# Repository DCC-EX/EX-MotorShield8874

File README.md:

# EX-Motorshield8874

## Overview

The EX-Motorshield8874 is a pin compatible with the original [Arduino Motor Shield Rev3](https://store.arduino.cc/products/arduino-motor-shield-rev3) but provides significantly improved electrical performance for driving higher loads, with lower power dissipation, and improved usability.

The EX-Motorshield8874 is based on two DRV8874 H-bridge motor drivers with integrated current sensing from Texas Instruments (TI). It is used to drive inductive loads like relays, solenoids, DC and stepping motors.

Powering of Arduino motherboard is possible due to the onboard DC/DC buck converter, supporting a wide input supply range from 9 to 30V. The reverse polarity protection prevents damage to the circuit and its components in case the power supply is accidentally connected with reversed polarity.

This Shield features a green status LED which provides a visual indication of the power supply status.

### Compatibility with [Arduino Motor Shield Rev3](https://store.arduino.cc/products/arduino-motor-shield-rev3)

The EX-MotorShield8874 is pin compatible with the original Arduino Motor Shield but provides significantly improved electrical performance for driving higher loads. Input voltage range is 9-30VDC and the maximum peak output is 5A per channel, in contrast to 5-12VDC and 2A peak for the original Arduino Motor Shield.

There is also almost no voltage drop incurred from the input voltage due to the MOSFET based design, unlike the bipolar L298 used in the Arduino Motor Shield. For DCC and DC PWM model railway use, a range of 10-24VDC is recommended depending on scale.

### Motor Driver Configuration for DCC-EX EX-CommandStation

The EX-MotorShield8874 will work with the `STANDARD_MOTOR_SHIELD` definitions in `MotorDrivers.h`, but that is not ideal for several reasons. It will both unnecessarily limit current output, ignore the fault pin, and not read current correctly.

The following motor definitions are required, and appear in later versions of EX-CommandStation, with the tag `EX8874_SHIELD`, which will differ according to whether the Command Station is an UNO or Mega with 5V 10-bit ADC, or a 3.3V capable system with 12-bit ADC:

```c++
// EX 8874 based shield connected to a 5V system (like Arduino UNO/Mega) and 10bit (1024) ADC
#define EX8874_SHIELD F("EX8874"), \
 new MotorDriver( 3, 12, UNUSED_PIN, 9, A0, 5.08, 5000, A4), \
 new MotorDriver(11, 13, UNUSED_PIN, 8, A1, 5.08, 5000, A5)

// EX 8874 based shield connected to a 3V3 system with 12-bit (4096) ADC
#define EX8874_SHIELD F("EX8874"), \
 new MotorDriver( 3, 12, UNUSED_PIN, 9, A0, 1.27, 5000, A4), \
 new MotorDriver(11, 13, UNUSED_PIN, 8, A1, 1.27, 5000, A5)
```

## Control Pin Assignments

### Default Pin Assignment for DCC-EX/Arduino motor control

The EX-MotorShield8874 has the following default pin assignment for control pins on the Arduino header, and is used for full Arduino Motor Shield R3 compatibility when used for DCC-EX EX-CommandStation.

| Function | Channel A Pin | Channel B Pin |
|-----------|-------|-------|
| PWM       | D3  | D11 |
| Direction | D12 | D13 |
| Brake     | D9  | D8 |
| Current sensing | A0 | A1 |
| Fault_N   | A4  | A5 |

Default pin assignment is used for DCC-EX command stations, and has the DRV8874 mode select pin `PMODE` = high.

### Alternative Pin Assignment for DCC-EX/Arduino motor control 

All motor control signals can be connected to two different Adruino header pins. Selecting between the default pin out and the alternative pin out is done via solder jumpers on the PCB which must be first cut to disable the default position, then solder applied to select the alternate position.

| Function | Channel A Pin | Channel B Pin |
|-----------|-------|-------|
| PWM       | D2  | D5 |
| Direction | D10 | D4 |
| Brake     | D7  | D6 |
| Current sensing | A2 | A3 |
| Fault_N   | D0  | D1 |

NB: For DCC-EX control, these are not ideal pin assignments and are intended for future support of stacking of two shields. Further documentation updates will be available once testing of this mode is complete.

### Fault indicator

The H-Bridges are protected against supply undervoltage, charge pump undervoltage, output overcurrent and device overtemperature. Fault conditions are indicated on the pin `nFAULT` of the H-Bridge driver. The open drain output of the fault indicator is pulled low during a fault condition and pulled to high with the on board pull-up resistor. There is one fault indicator per channel.

**NOTE for UNO users:** the `nFAULT` pins are routed to the same pins used for I2C on the ATMEGA329P used on the Arduino UNO R3, namely A4 and A5. As such, if you are to use an EX-MotorShield8874 on an Arduino UNO, please cut the default track on the relevant jumpers to disable them. If you want to use the `nFault` pins you will need to manually jumper them to any available alternate digital input pins, then configure the Motor Driver entry in EX-CommandStation to suit the pins used.

### Alternative pin assignment for other motor control applications

The alternative pin assignment for motor control (PH/EN mode) allows to control the motor in a speed and direction type interface. This mode is selected via Jumper J101 (DRV8874 mode select pin `PMODE` = low) and is NOT required for use with DCC-EX. It is documented for completeness.

| Function | Channel A Pin | Channel B Pin |
|-----------|-------|-------|
| PH       | D3  | D11 |
| EN       | D12 | D13 |
| Brake     | D9  | D8 |
| Current sensing | A0 | A1 |
| Fault_N   | A4  | A5 |

## Electrical Parameters

The DCC-EX Motor Shield provides the following electrical parameters.

| Parameter | Value |
|-----------|-------|
| Operating voltage range | 9-30VDC, polarity protected|
| Maximum H-bridge current  | 5A peak per channel |
| Arduino supply voltage output (VIN) | 7.2V@2A max |
| IO voltage              | 3.3 and 5V, using IOREF by default |
| I2C connectivity        | Dupont, 2.54mm dual row pin, and STEMMA QT/Qwiic Headers |
| Current sensing         | Yes, adjusts range to IOREF voltage |
| Control modes possible | PWM, by default, PH/EN via jumper |

## Current Sensing

Current sensing is independently available for each channel. The Arduino IOREF supply voltage is sensed automatically, and adjusts the gain factor for the current sensing to take advantage of the full ADC input voltage range for 5V or 3.3V microcontrollers. The sense factors are calculated as follows for DCC-EX motor driver definitions:

| IOREF Voltage: | 5V | 3V3 |
|----------------|----|-----|
| 10-bit ADC, 1024 count | 5.08 | 4.94 |
| 12-bit ADC, 4096 count | 1.27 | 1.24 |

These values have been incorporated into EX-CommandStation Motor Driver definitions, so selecting `EX8874_SHIELD` as the `MOTOR_SHIELD_TYPE` in config.h will configure it correctly.

## Track LEDs

LEDs are provided for each channel, indicating the corresponding H-Bridge is supplying power to output connectors.

## Header Pin Assignments

The following pin assignments have been used for the various connectors.

### I2C Headers

Three I2C expansion headers (Dupont, dual-row 8-pin, and STEMMA QT/Qwiic) allow connecting either an OLED display or other additional I2C based devices.

#### Arduino Header

On the Arduino header, the default upper right I2C pins are used for I2C:

| Function | UNO R3 Pin | Mega Pin |
|-----------|-------|-------|
| SCL | D18/A5 | D21 |
| SDA | D19/A4 | D20 |

#### DIP Header

The dual-row 8-pin header has the following pin assignments:

| Function | Odd Pin | Even Pin |
|-----------|-------|-------|
| IOREF | 1 | 2 |
| SDA | 3 | 4 |
| GND | 5 | 6 |
| SCL | 7 | 8 |

#### OLED Header

The single-row 4-pin OLED header has the following pin assignments, which are standard for many I2C capable OLED displays:

| Function | Pin |
|-----------|-------|
| GND | 1 |
| IOREF | 2 |
| SCL | 3 |
| SDA | 4 |

#### STEMMA QT/Qwiic Connector

STEMMA QT/Qwiic connector pin assignments are per the standard, but included for completeness:

| Function | Pin | Colour Code |
|-----------|-------|-------|
| GND | 1 | Black |
| 3v3 | 2 | Red |
| SDA | 3 | Blue |
| SCL | 4 | Yellow |

**NOTE** STEMMA QT power is tied to 3v3 as that is required for the standard. When using the EX-MotorShield8874 with 5V motherboards such as UNO and Mega, any I2C peripherals connected to the STEMMA QT connector **must** be 5V-tolerant only!

Pull-up resistors for the I2C communication are not populated by default. If required, pull-up resistors (R101, R102) can be populated on the board, though this is typically not necessary.

## Reset button

A reset button is provided to reset the Arduino board.

## PCB Jumpers

Various PCB jumpers are provided to alter functionality of the board to suit user needs. These include jumpers to alter pin assignments for driving the motor shield, to disable the onboard 7.2V regulator or disconnect it from the VIN, and jumpers to override the IOREF pin for ADC range selection.

### Aternate Pin Assignment PCB Jumpers

There are 5 sets of PCB jumpers for each motor driver IC, some or all of which can be used to reassign Arduino pins to the various logic functions. The table below lists them in order as they appear on the PCB:

| Function | Driver A Default | Driver A Alternate| Driver B Default | Driver B Alternate |
|----------|---------|----------|---------|-----------|
| PWM       | D3  | D2 | D11 | D5 |
| Fault | A4  | D0 | A5 | D1 |
| Brake | D9  | D7 | D8 | D6 |
| Direction | D12 | D10 | D13 | D4 |
| Current sense | A0 | A2 | A1 | A3 |

### Power Configuration PCB Jumpers

There are 4 sets of PCB jumpers to change the way power is handled on the board. One on the top of the board, and 3 on the bottom, shown here:

| Jumper | Function |
|--------|----------|
| Regulator Disable (Regulator Enable on Rev A boards) | Defaults to *ENABLED*. Rev B boards, *solder* between pads to DISABLE onboard 7.2V regulator. Rev A boards *cut* between pads to DISABLE |
| IOREF Override | Defaults to IOREF used as power source, cut and then solder to either 5V or 3V3 to power logic and current sense |
| VM to Vin Enable (unlabelled on Rev A boards) | Defaults to NOT connected. CAUTION: soldering these pads CONNECTS motor power to VIN and should not be needed |
| VIN | Defaults to ON, cut to stop providing regulated 7.2V power to VIN to power the Arduino |

## Manufacturing Notes

### Bill of Materials (BOM)

The bill of materials spreadsheet above is optimised for manufacture at JLCPCB (https://jlcpcb.com/) at present, and will allow assembly of all components except the DC barrel jack, motor output connectors and Arduino shield stackable headers.

### PCB Material Specifications

For best performance, 1oz copper for both outer and inner layers of this 4-layer PCB are safest. Of course 2oz copper can be specified, but this is not deemed necessary from testing so far and cost may be prohibitive. Also, using FR-4 TG155 will give additional safety margin. The design can be made lead-free, provided all components are also lead-free types. JLCPCB currently does not have lead-free connectors for DCC track or DC input power, so those components are not in the default Bill of Materials (BOM).

## Stacking Multiple Shields

It is possibile to stack two EX-MotorShield8874s, and even stack an EX-MotorShield and a Arduino Motor Shield.

There are two different proposed operating modes possible:

1. **Independent district mode:** The DCC-EX Motor Shields are controlled independently using different control signals. This allows a total 4 independent H-Bridges to be driven completely independently for separate DCC or DC PWM districts.
2. **Parallel booster mode:** Both EX-MotorShield8874s are controlled with the same control signals so both pairs of H-bridges are running in parallel. This mode is used to increase the current capabilities of the 2 DCC or DC PWM districts.

***CAUTIONARY NOTE:*** Only one EX-MotorShield8874 should provide power to the underlying motherboard from the DCC power feed! The jumper connecting the top VIN feed pin from the onboard 7.2V regulator to the Arduino sheild connectors must be cut on one of the stacked shields. It is also advisable to cut the ENABLE pin for the onboard regulator as that will turn it off completely as well. (See documentation of Power Configuration PCB Jumpers, above!)

This information is provided for reference. For full documentation, please visit this section on our website; [Stacking EX-MotorShields](https://dcc-ex.com/reference/hardware/motorboards/ex-motor-shield-8874.html#stacking-ex-motorshield8874s)

## Version History

**Rev B2**
* Changed the AOD4185 reverse voltage protection mosfet (Q201) in a TO-252-2 package to an AO4407C in an SOIC-8 package to save board space.

**Rev B**
* Changed 7.2V Regulator from MP9942GJ-Z to TPS54302 due to availability issues. NOTICE: This forced the Regulator Enable/Disable to be reversed from the Rev A board. The Rev A board jumper pad must be *cut* to disable the regulator and is named "Regulator Enable". On the Rev B board, the jumper must be *solder bridged* to to disable the regulator and is labelled "7V Regulator Disable".
* The regulator change necessitated changing Inductor L201 from 56uH to 15uH.

**Rev A2**
* Added 47k pulldown resistors (R103 and R104) to the enable pins to prevent possible DCC or DC voltage pulses to the outputs until the command station is able to set the GPIO pins to a stable state during boot up.
* Added more descriptive silkscreen labelling.
* Removed solder mask from jumper pads to make it easier to see which are bridged and which are open.

**Rev A**
* First version of the EX-MotorShield8874. NOTICE: It may be necessary to add 47k pulldown resistors between pwm_a and pwm_b and GND. These are the "enable" pins that turn power on to the track outputs. With the pins floating, it is possible that brief DC power can be applied to the track until the command station fully boots. If configured for the STANDARD_MOTOR_SHIELD, this is as simple as inserting one end of a resistor into pin 3 of the header and the other end to a GND header pin, and the other resister between pin 11 and GND. If using a different motor driver definition, use the enable pins for that definition.

## Reference

- [Schematic](./static_images/EX-MotorShield8874Schematic_RevB2.pdf)
- [DRV8874 Datasheet](https://www.ti.com/product/DRV8874?keyMatch=DRV8874&tisearch=search-everything&usecase=GPN)

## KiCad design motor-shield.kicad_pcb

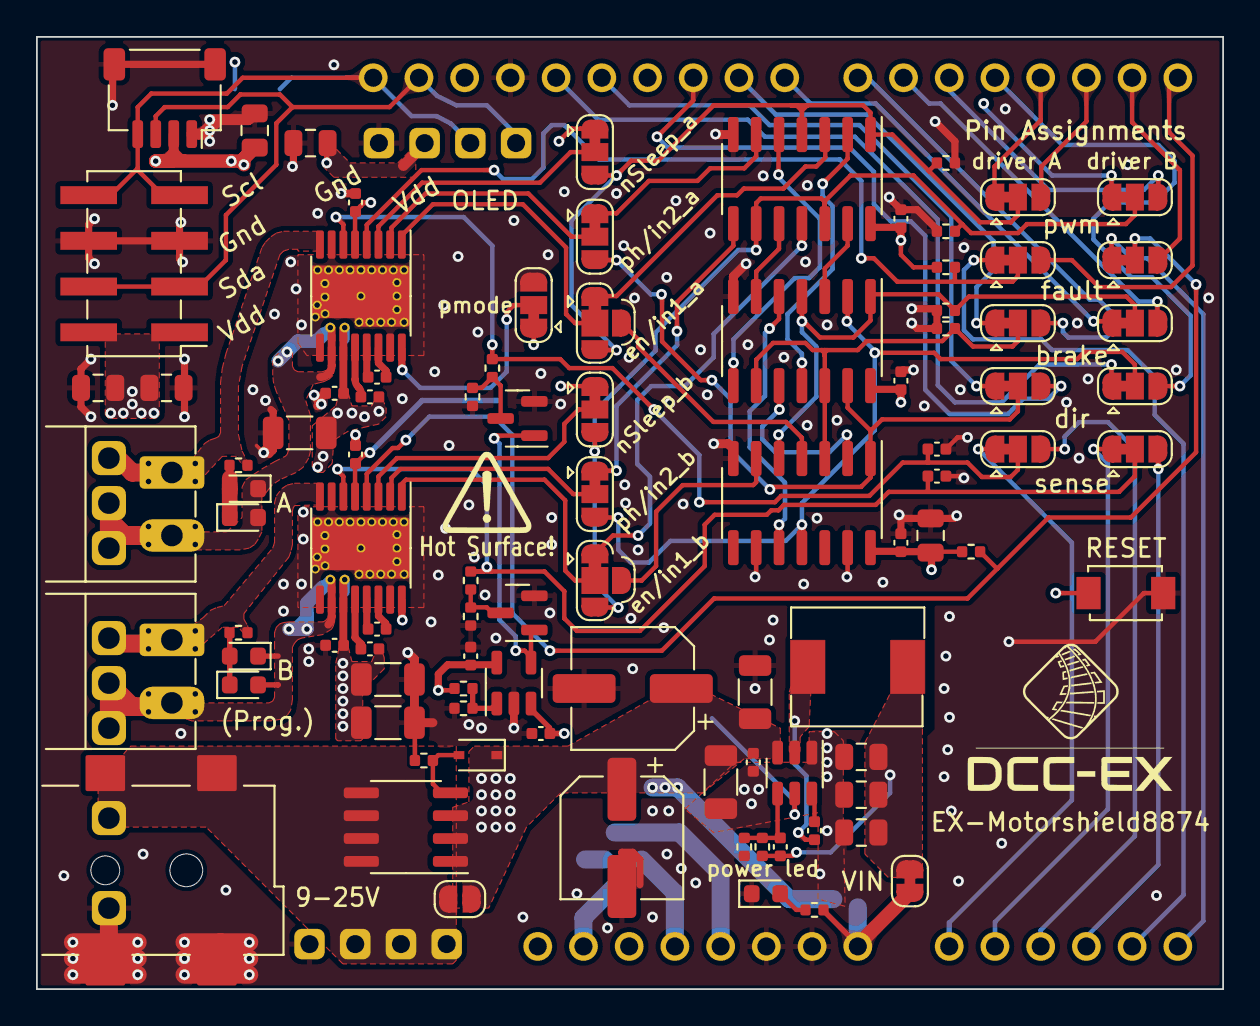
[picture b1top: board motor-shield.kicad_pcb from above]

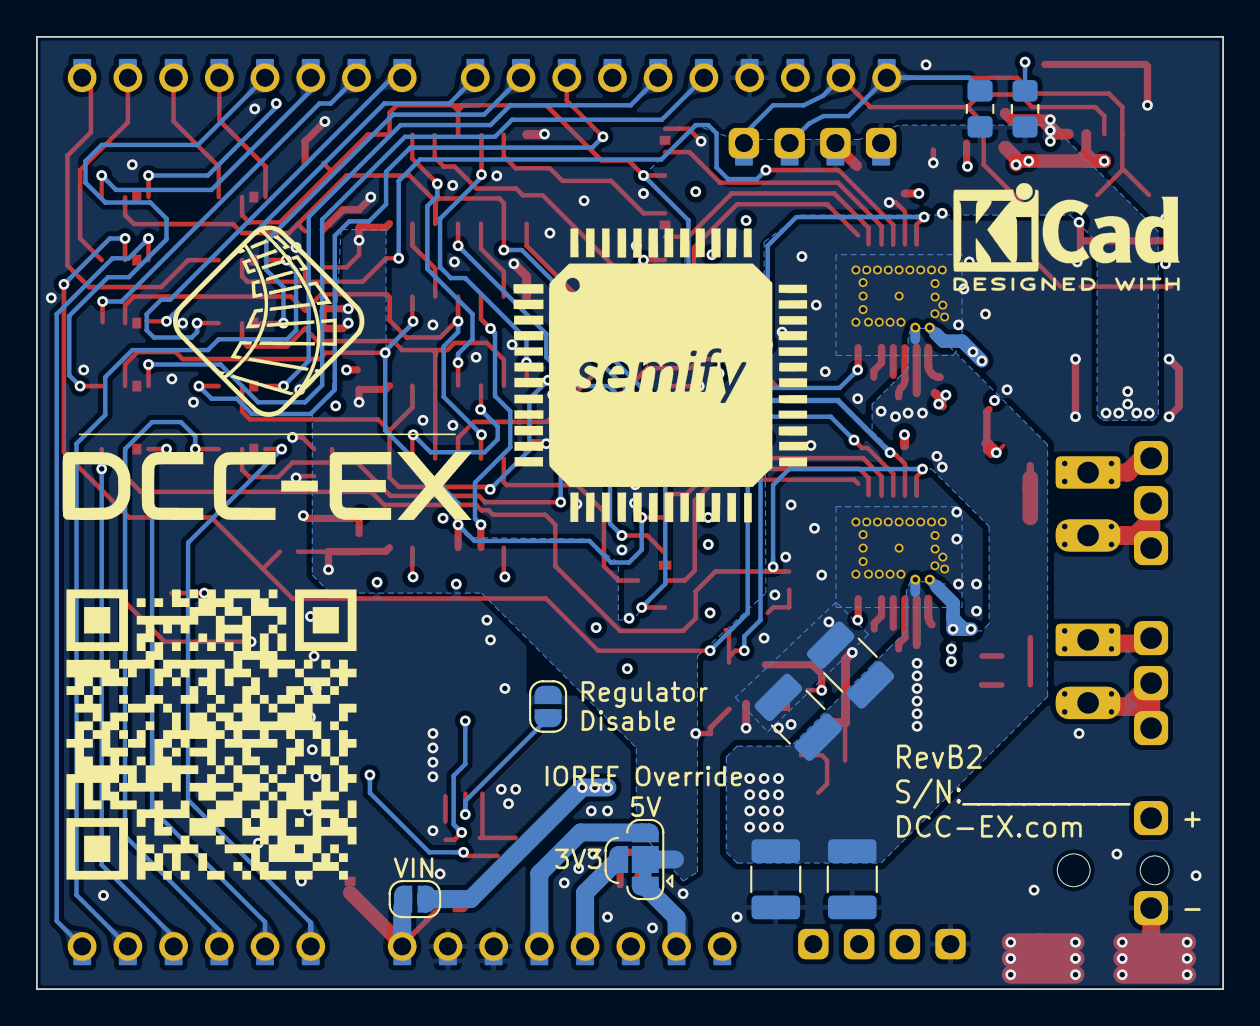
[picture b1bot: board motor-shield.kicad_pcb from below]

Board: 4 copper layers, 65.9 x 52.9 mm, 108 parts (10 on the bottom side), 83 nets.

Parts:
A101: Arduino_UNO_R3; Arduino_UNO_R3_edit
C101, C104, C107, C108, C114, C115, C208, C220, C221, C222: 100n; C_1005_(0402)
C102, C105, C203, C209, C210: 10u VM; C_1206_3216Metric
C103, C106, C211: 100n VM; C_1005_(0402)
C109, C110: 22n VM; C_1005_(0402)
C111, C212, C213, C214, C216, C217, C218, C219: 22u; C_0805_2012Metric
C112, C113: 22n; C_1005_(0402)
C201, C202: 100u VM; CP_Elec_6.3x7.7
C204, C205, C206, C207: -; C_1210_3225Metric_Pad1.33x2.70mm_HandSolder
C215: 56p; C_1005_(0402)
D101, D102, D103, D104: 0603_LED_Yellow; LED_0603_1608Metric
D201: 10V; D_SOD-323
D202: 0603_LED_Green; LED_0603_1608Metric
J101, J103: MC 1,5/ 2-G-3,5; PhoenixContact_MC_1,5_2-G-3.5_1x02_P3.50mm_Horizontal_edited
J102, J104: -; PinHeader_01x03_P2.5mm_Vertical_min
J105: STEMMA QT; JST_SH_SM04B-SRSS-TB_1x04-1MP_P1.00mm_Horizontal
J106: Conn_02x04_smd; PinHeader_2x04_P2.54mm_Vertical_SMD
J107: Conn_01x04_f; PinHeader_1x04_P2.54mm_Vertical_solderpad
J201: Barrel_Jack_MountingPin; BarrelJack_2.1mm_SMD
J202: -; PinHeader_01x02_P5mm_Vertical_min
J203: -; PinHeader_1x04_P2.54mm_Vertical_min_1
JP101, JP102, JP103, JP105, JP106, JP108, JP109, JP110, JP111, JP112, JP113, JP114, JP115, JP116, JP117: Jumper_3; SolderJumper-3
JP104, JP107, JP205: Jumper_4; SolderJumper-4
JP201, JP202, JP204: Jumper_2_o; SolderJumper-2_P1.3mm_Open_RoundedPad1.0x1.5mm
JP203: Jumper_2; SolderJumper-2_P1.3mm_Bridged
L201: 15uH; L_7.1x6.6_H3_SLO0630H
Q101, Q102: AO3400A; SOT-23
Q201: AO4407C; SOIC-8_3.9x4.9mm_P1.27mm
R101, R102, R103, R104, R107, R108, R109, R110, R201, R202: 47k; R_1005_(0402)
R105, R106: 10k; R_0805_2012Metric_Pad1.20x1.40mm_HandSolder
R111, R112: 1k43; R_1005_(0402)
R113, R114: 732R; R_1005_(0402)
R115, R204: 9k1; R_1005_(0402)
R116, R203: 100k; R_1005_(0402)
SW101: Switch; SW_SPST_TS-1088-AR02016
U101: 74HC04; SO-14_3.9x8.65mm_P1.27mm
U102: 74HC08; SO-14_3.9x8.65mm_P1.27mm
U103: 74HC32; SO-14_3.9x8.65mm_P1.27mm
U104, U105: DRV8874PWPR; HTSSOP-16-1EP_4.4x5mm_P0.65mm_EP3.4x5mm_Mask2.46_HiAmp
U106: LMV321; SOT-23-5
U201: TPS54302; SOT-23-6

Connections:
+3V3: A101.4 (3V3), C111.1, J105.2, JP205.4 (D)
+5V: A101.5 (+5V), C114.2, JP205.3 (B), R115.1, U106.5 (V+)
/4V5: R115.2, R116.1, U106.1 (+)
/Power/bst: C208.1, U201.6 (BOOT)
/Power/en2: JP204.2 (B), U201.5 (EN)
/Power/fn: C215.1, R203.2, R204.1, U201.4 (FB)
/Power/gate: D201.2 (A), Q201.4 (G), R201.1
/Power/sw: C208.2, L201.1, U201.2 (SW)
/Power/v_conn: J201.1, J202.1, J203.1, JP201.1 (A), Q201.5 (D), Q201.6 (D), Q201.7 (D), Q201.8 (D)
/Power/vin: C212.1, C213.1, C214.1, C215.2, JP203.1 (A), L201.2, R203.1
/alt_brake_a: A101.22 (D7), JP108.3 (B)
/alt_brake_b: A101.21 (D6), JP109.3 (B)
/alt_direction_a: A101.25 (D10), JP110.3 (B)
/alt_direction_b: A101.19 (D4), JP111.3 (B)
/alt_fault_n_a: A101.15 (D0/RX), JP105.3 (B)
/alt_fault_n_b: A101.16 (D1/TX), JP106.3 (B)
/alt_pwm_a: A101.17 (D2), JP102.3 (B)
/alt_pwm_b: A101.20 (D5), JP103.3 (B)
/alt_sen_a: A101.11 (A2), JP113.3 (B)
/alt_sen_b: A101.12 (A3), JP114.3 (B)
/brake_a: JP108.2 (C), R101.1, U101.3, U103.9, U103.12
/brake_a_n: JP104.4 (D), U101.4
/brake_b: JP109.2 (C), R102.1, U101.5, U103.1, U103.4
/brake_b_n: JP107.4 (D), U101.6
/cpha: C109.2, U104.13 (CPH)
/cphb: C110.2, U105.13 (CPH)
/cpla: C109.1, U104.14 (CPL)
/cplb: C110.1, U105.14 (CPL)
/def_brake_a: A101.24 (D9), JP108.1 (A)
/def_brake_b: A101.23 (D8), JP109.1 (A)
/def_direction_a: A101.27 (D12), JP110.1 (A)
/def_direction_b: A101.28 (D13), JP111.1 (A)
/def_fault_n_a: A101.13 (SDA/A4), JP105.1 (A)
/def_fault_n_b: A101.14 (SCL/A5), JP106.1 (A)
/def_pwm_a: A101.18 (D3), JP102.1 (A)
/def_pwm_b: A101.26 (D11), JP103.1 (A)
/def_sen_a: A101.9 (A0), JP113.1 (A)
/def_sen_b: A101.10 (A1), JP114.1 (A)
/direction_a: JP110.2 (C), JP112.3 (B), U101.1, U103.13
/direction_a_n: U101.2, U103.10
/direction_b: JP111.2 (C), JP115.3 (B), U101.11, U103.2
/direction_b_n: U101.10, U103.5
/en/in1a: JP104.2 (C), U104.1 (EN/IN1)
/en/in1b: JP107.2 (C), U105.1 (EN/IN1)
/fault_n_a: JP105.2 (C), R109.2, U104.4 (nFAULT)
/fault_n_b: JP106.2 (C), R110.2, U105.4 (nFAULT)
/in1_a: JP104.1 (A), U102.3
/in1_b: JP107.1 (A), U102.11
/in2_a: JP112.1 (A), U102.6
/in2_b: JP115.1 (A), U102.8
/ioref_is_3V3_not_5V: Q101.1 (G), Q102.1 (G), U106.4
/nSleepa: JP116.2 (C), U104.3 (nSleep)
/nSleepb: JP117.2 (C), U105.3 (nSleep)
/or_1a: U102.2, U103.11
/or_1b: U102.13, U103.3
/or_2a: U102.5, U103.8
/or_2b: U102.10, U103.6
/out1a: J101.1, J102.1, R107.2, U104.8 (OUT1)
/out1b: J103.1, J104.1, R108.2, U105.8 (OUT1)
/out2a: D101.2 (A), D102.1 (K), J101.2, J102.2, U104.10 (OUT2)
/out2b: D103.2 (A), D104.1 (K), J103.2, J104.2, U105.10 (OUT2)
/ph/in2a: JP112.2 (C), U104.2 (PH/IN2)
/ph/in2b: JP115.2 (C), U105.2 (PH/IN2)
/pmode: JP101.2 (C), U104.16 (PMODE), U105.16 (PMODE)
/pwm_a: JP102.2 (C), JP104.3 (B), JP116.3 (B), R103.1, U102.1, U102.4
/pwm_b: JP103.2 (C), JP107.3 (B), JP117.3 (B), R104.1, U102.9, U102.12
/reset: A101.3 (~RESET), SW101.1
/scl: A101.32 (SCL/A5), J105.4, J106.7, J106.8, J107.3, R106.2
/sda: A101.31 (SDA/A4), J105.3, J106.3, J106.4, J107.4, R105.2
/sen_a: C112.1, JP113.2 (C), R111.1, U104.6 (IPROPI)
/sen_b: C113.1, JP114.2 (C), R112.1, U105.6 (IPROPI)
/sen_switch_a: Q101.3 (D), R111.2, R113.1
/sen_switch_b: Q102.3 (D), R112.2, R114.1
/vcpa: C107.2, U104.12 (VCP)
/vcpb: C108.2, U105.12 (VCP)
GND: A101.6 (GND), A101.7 (GND), A101.29 (GND), C101.2, C102.2, C103.2, C104.2, C105.2, C106.2, C111.2, C112.2, C113.2, C114.1, C115.1, C201.2, C202.2, C203.2, C204.2, C205.2, C206.2, C207.2, C209.2, C210.2, C211.2, C212.2, C213.2, C214.2, C216.2, C217.2, C218.2, C219.2, C220.2, C221.2, C222.2, D202.1 (K), J105.1, J105.MP (MountPin), J106.5, J106.6, J107.1, J201.2, J201.MP (MountPin), J202.2, J203.2, JP101.3 (B), JP204.1 (A), Q101.2 (S), Q102.2 (S), R101.2, R102.2, R103.2, R104.2, R113.2, R114.2, R116.2, R201.2, R204.2, SW101.2, U101.7 (GND), U101.9, U101.13, U102.7 (GND), U103.7 (GND), U104.7 (IMODE), U104.9 (GND), U104.15 (GND), U104.17 (GND), U105.7 (IMODE), U105.9 (GND), U105.15 (GND), U105.17 (GND), U106.2 (V-), U201.1 (GND)
IOREF: C101.1, C104.1, C115.2, C216.1, C217.1, C218.1, C219.1, C220.1, C221.1, C222.1, J106.1, J106.2, J107.2, JP101.1 (A), JP116.1 (A), JP117.1 (A), JP205.2 (C), R105.1, R106.1, R109.1, R110.1, U101.14 (VCC), U102.14 (VCC), U103.14 (VCC), U104.5 (VRef), U105.5 (VRef), U106.3 (-)
unnamed: D101.1 (K), D102.2 (A), R107.1
unnamed: D103.1 (K), D104.2 (A), R108.1
unnamed: D202.2 (A), R202.1
VIN: A101.8 (VIN), JP202.2 (B), JP203.2 (B), R202.2
VM: C102.1, C103.1, C105.1, C106.1, C107.1, C108.1, C201.1, C202.1, C203.1, C204.1, C205.1, C206.1, C207.1, C209.1, C210.1, C211.1, D201.1 (K), JP201.2 (B), JP202.1 (A), Q201.1 (S), Q201.2 (S), Q201.3 (S), U104.11 (VM), U105.11 (VM), U201.3 (VIN)
ioref: A101.2 (IOREF), JP205.1 (A)

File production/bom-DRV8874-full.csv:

"Designator","Footprint","Quantity","Value","LCSC Part #"
"C101, C104, C107, C108, C114, C115, C208, C220, C221, C222","C_1005_(0402)",10,"100n","C1525"
"C102, C105, C203, C209, C210",1206,5,"10u VM","C13585"
"C103, C106, C211","C_1005_(0402)",3,"100n VM","C307331"
"C109, C110","C_1005_(0402)",2,"22n VM","C337699"
"C111, C212, C213, C214, C216, C217, C218, C219",805,8,"22u","C45783"
"C112, C113","C_1005_(0402)",2,"22n","C337699"
"C201, C202","CP_Elec_6.3x7.7",2,"100u VM","C2972719 "
"C215","C_1005_(0402)",1,"56p","C107007"
"D101, D102, D103, D104",603,4,"0603_LED_Yellow","C72038"
"D201","D_SOD-323",1,"10V","C85383"
"D202",603,1,"0603_LED_Green","C72043 "
"J101, J103","PhoenixContact_MC_1,5_2-G-3.5_1x02_P3.50mm_Horizontal_edited",2,"MC 1,5/ 2-G-3,5","C409115"
"J105","JST_SH_SM04B-SRSS-TB_1x04-1MP_P1.00mm_Horizontal",1,"STEMMA QT","C160404"
"J106","PinHeader_2x04_P2.54mm_Vertical_SMD",1,"Conn_02x04_smd","C780053"
"J107","PinHeader_1x04_P2.54mm_Vertical_solderpad",1,"Conn_01x04_f"," C2685089"
"J201","BarrelJack_2.1mm_SMD",1,"Barrel_Jack_MountingPin","C319134 "
"L201","L_7.1x6.6_H3_SLO0630H",1,"15uH","C182182 "
"Q101, Q102","SOT-23",2,"AO3400A","C20917"
"Q201","SOIC-8_3.9x4.9mm_P1.27mm",1,"AO4407C","C469397"
"R101, R102, R103, R104, R107, R108, R109, R110, R201, R202","R_1005_(0402)",10,"47k","C163440"
"R111, R112","R_1005_(0402)",2,"1k43","C226851"
"R113, R114","R_1005_(0402)",2,"732R","C321605"
"R115, R204","R_1005_(0402)",2,"9k1","C25926"
"R116, R203","R_1005_(0402)",2,"100k","C60491"
"SW101","SW_SPST_TS-1088-AR02016",1,"Switch","C720477"
"U101","SO-14_3.9x8.65mm_P1.27mm",1,"74HC04","C5590"
"U102","SO-14_3.9x8.65mm_P1.27mm",1,"74HC08","C5593"
"U103","SO-14_3.9x8.65mm_P1.27mm",1,"74HC32","C5632"
"U104, U105","HTSSOP-16-1EP_4.4x5mm_P0.65mm_EP3.4x5mm_Mask2.46_HiAmp",2,"DRV8874PWPR","C1855818"
"U106","SOT-23-5",1,"LMV321","C7972"
"U201","SOT-23-6",1,"TPS54302","C311983"

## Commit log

2023-04-27 contribute motorshield
2023-05-04 README edits for clarity and accuracy
2023-05-04 README fixes
2023-05-04 More README edits
2023-05-04 README readability improvements
2023-05-05 Further README edits
2023-05-05 Yet more edits!
2023-05-05 README - added I2C pins
2023-05-05 README formatting
2023-05-05 README notes for UNO users
2023-05-05 README - edits re shield definition in DCC-EX
2023-05-05 README - typos and text position
2023-05-08 README edits for jumpers
2023-05-08 README edits
2023-05-08 README pin assignments
2023-05-08 README jumper doco
2023-05-08 README jumpers
2023-05-08 README power jumpers
2023-05-09 README power config
2023-05-09 README jumper config
2023-05-09 README BOM notes
2023-05-09 README image tweaks
2023-05-15 PCB Manufacturing notes
2023-06-02 remove bom and pos files from gerbers.zip and move bom and pos files to production folder
2023-06-02 Add gitignore file
2023-06-02 Create LICENSE
    Add license file
2023-06-05 Update to RevA1
2023-06-26 Add pulldowns and make all pulldowns larger
2023-06-26 Move new resistor silkscreen out of the way
2023-07-08 Rev A2
2023-08-07 README update fault pin definitions
    Changed in CommandStation-EX:
    132b077 ("Fault pin handling made more straight forward", 2023-05-20)
2024-01-24 update to RevB
2024-05-06 Update README.md
    Add a detailed version history
2024-05-07 Update README.md
    Fix motor driver config from negative fault pin values to positive
2024-05-07 Rename ex-motorshield-jumper-pads.png to ex_motorshield_jumper_pads.png
2024-05-07 Rename ex_motorshield_jumper_pads.png to ex-motorshield-jumper-pads.png
2024-05-07 Rename ex_motorshield_power_config-jumpers_bottom.png to ex-motorshield-power-config-jumpers-bottom.png
2024-05-07 Rename ex_motorshield_power_config_2.png to ex-motorshield-power-config-bottom.png
2024-05-07 Added Motorshield schematic link to readme
2024-05-07 Update README.md
    Correct jumper pad table help
2024-07-08 Create readme.txt
    Add folder and readme for 3d step files
2024-07-08 Add 8874 3d step file
